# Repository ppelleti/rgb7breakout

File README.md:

Don't use this as-is; the footprint for D2 is wrong.

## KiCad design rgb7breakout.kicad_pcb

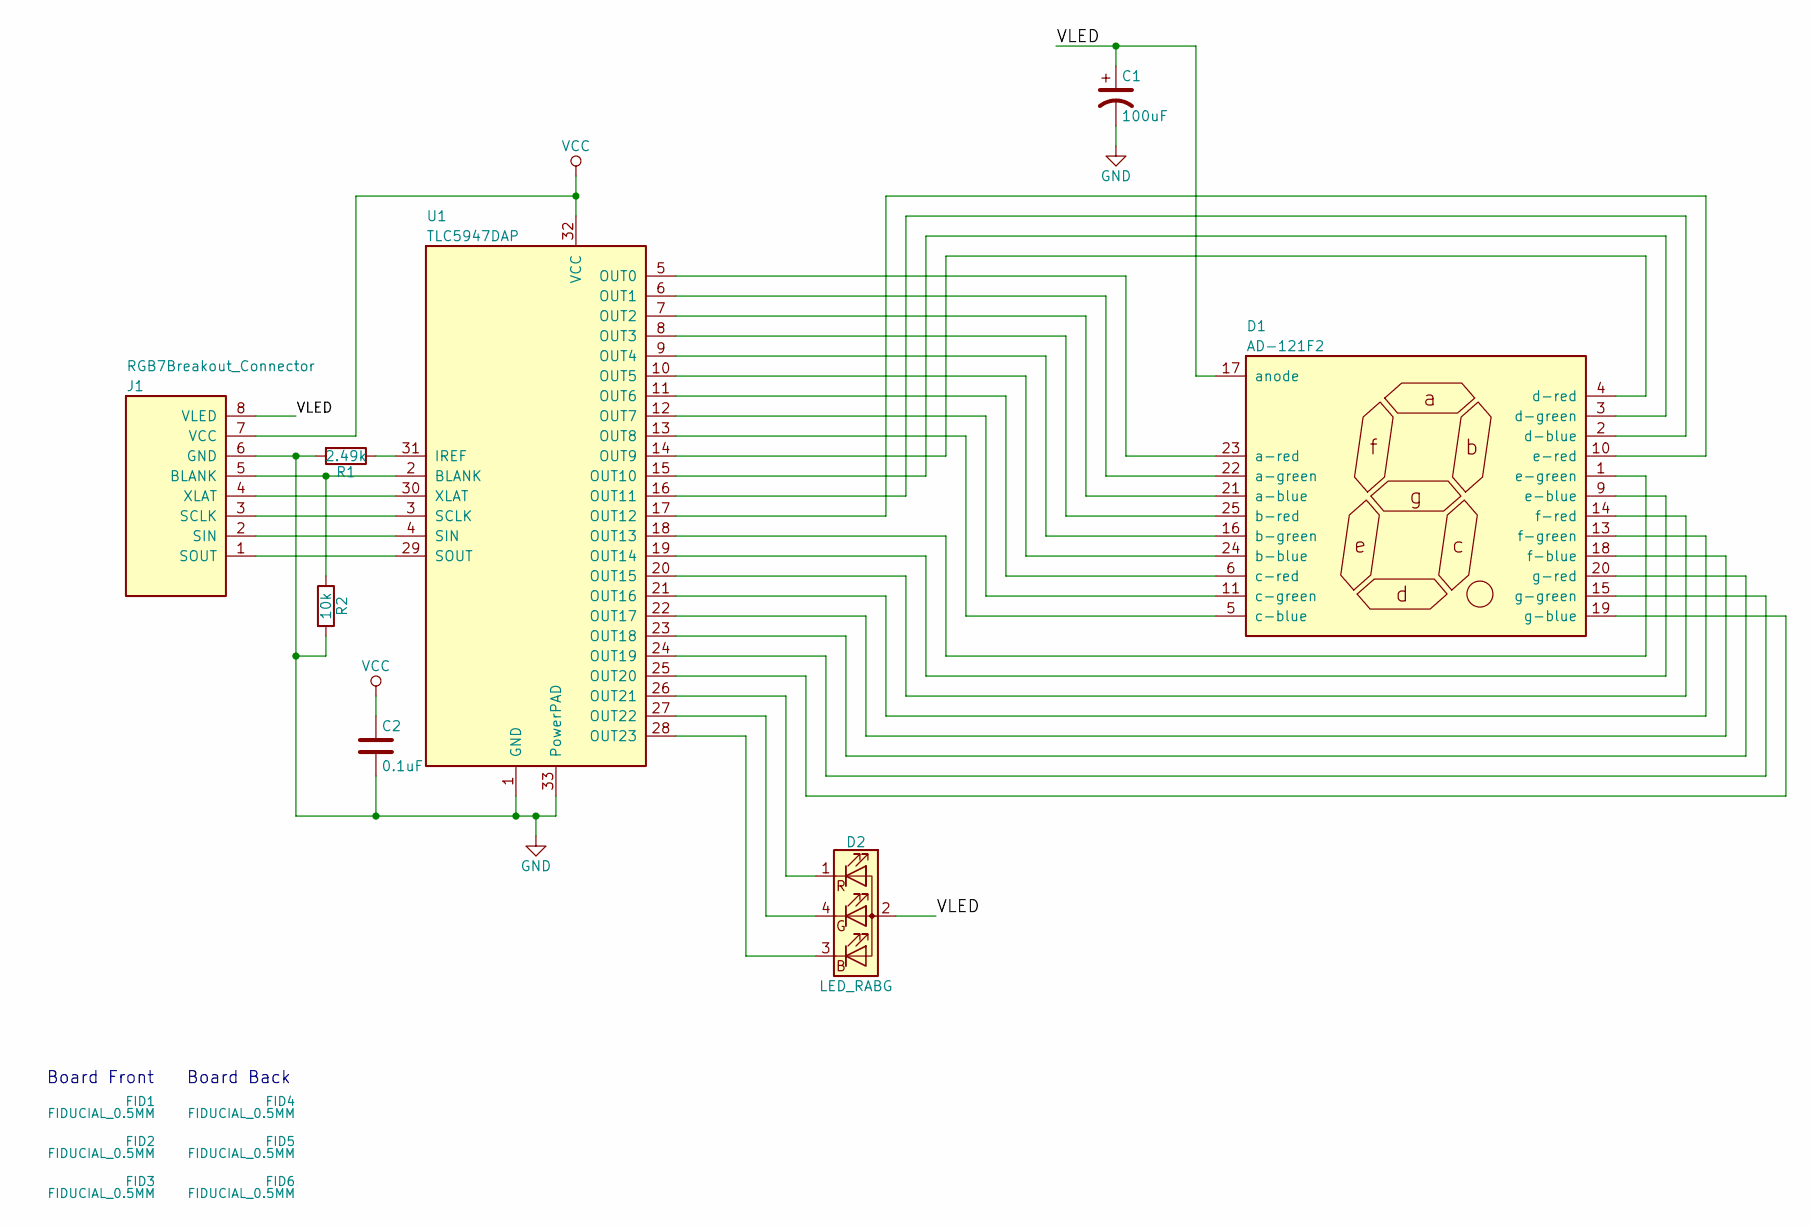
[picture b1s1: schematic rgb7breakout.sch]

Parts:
C1: 100uF; CP_Elec_6.3x7.7; mpn 107SML016M
C2: 0.1uF; C_0603; mpn MF-CAP-0603-0.1uF
D1: AD-121F2; mpn AD-121F2
D2: LED_RABG; LED_Cree-PLCC4; mpn CLV1A-FKB-CHMKPEHBB7A363
FID1, FID2, FID3, FID4, FID5, FID6: FIDUCIAL_0.5MM; MF_Aesthetics-FIDUCIAL_0.5MM
J1: RGB7Breakout_Connector; Pin_Header_Angled_1x08_Pitch2.54mm; mpn PRPC008SBAN-M71RC
R1: 2.49k; R_0603; mpn RC0603FR-072K49L
R2: 10k; R_0603; mpn MF-RES-0603-10K
U1: TLC5947DAP; HTSSOP-32_6.1x11mm_Pitch0.65mm_ThermalPad; mpn TLC5947DAP

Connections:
/VLED: C1.1, D1.17 (anode), D2.2 (A), J1.8 (VLED)
GND: C1.2, C2.2, J1.6 (GND), R1.2, R2.2, U1.1 (GND), U1.33 (PowerPAD)
unnamed: D1.1 (e-green), U1.18 (OUT13)
unnamed: D1.2 (d-blue), U1.16 (OUT11)
unnamed: D1.3 (d-green), U1.15 (OUT10)
unnamed: D1.4 (d-red), U1.14 (OUT9)
unnamed: D1.5 (c-blue), U1.13 (OUT8)
unnamed: D1.6 (c-red), U1.11 (OUT6)
unnamed: D1.9 (e-blue), U1.19 (OUT14)
unnamed: D1.10 (e-red), U1.17 (OUT12)
unnamed: D1.11 (c-green), U1.12 (OUT7)
unnamed: D1.13 (f-green), U1.21 (OUT16)
unnamed: D1.14 (f-red), U1.20 (OUT15)
unnamed: D1.15 (g-green), U1.24 (OUT19)
unnamed: D1.16 (b-green), U1.9 (OUT4)
unnamed: D1.18 (f-blue), U1.22 (OUT17)
unnamed: D1.19 (g-blue), U1.25 (OUT20)
unnamed: D1.20 (g-red), U1.23 (OUT18)
unnamed: D1.21 (a-blue), U1.7 (OUT2)
unnamed: D1.22 (a-green), U1.6 (OUT1)
unnamed: D1.23 (a-red), U1.5 (OUT0)
unnamed: D1.24 (b-blue), U1.10 (OUT5)
unnamed: D1.25 (b-red), U1.8 (OUT3)
unnamed: D2.1 (RK), U1.26 (OUT21)
unnamed: D2.3 (BK), U1.28 (OUT23)
unnamed: D2.4 (GK), U1.27 (OUT22)
unnamed: J1.1 (SOUT), U1.29 (SOUT)
unnamed: J1.2 (SIN), U1.4 (SIN)
unnamed: J1.3 (SCLK), U1.3 (SCLK)
unnamed: J1.4 (XLAT), U1.30 (XLAT)
unnamed: J1.5 (BLANK), R2.1, U1.2 (BLANK)
unnamed: R1.1, U1.31 (IREF)
VCC: C2.1, J1.7 (VCC), U1.32 (VCC)

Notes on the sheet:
Board Front
Board Back

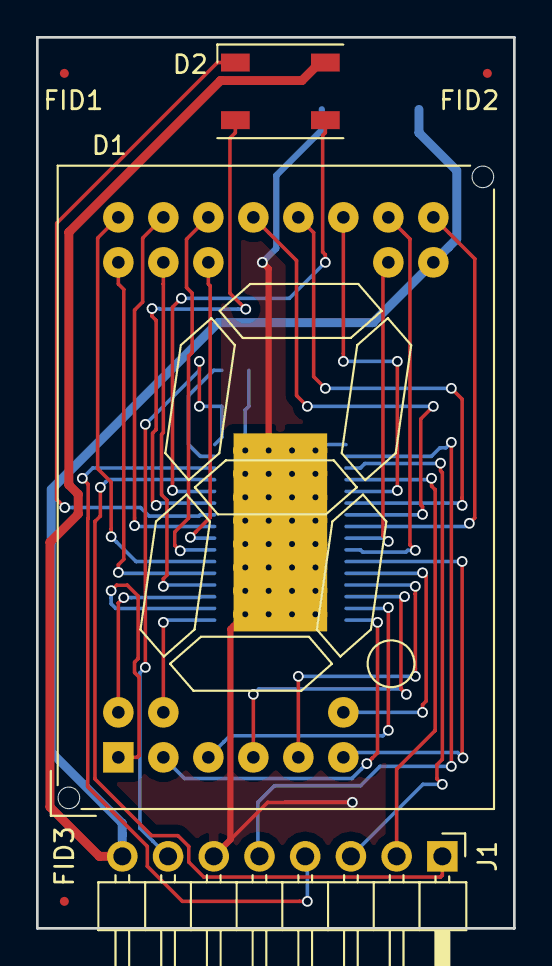
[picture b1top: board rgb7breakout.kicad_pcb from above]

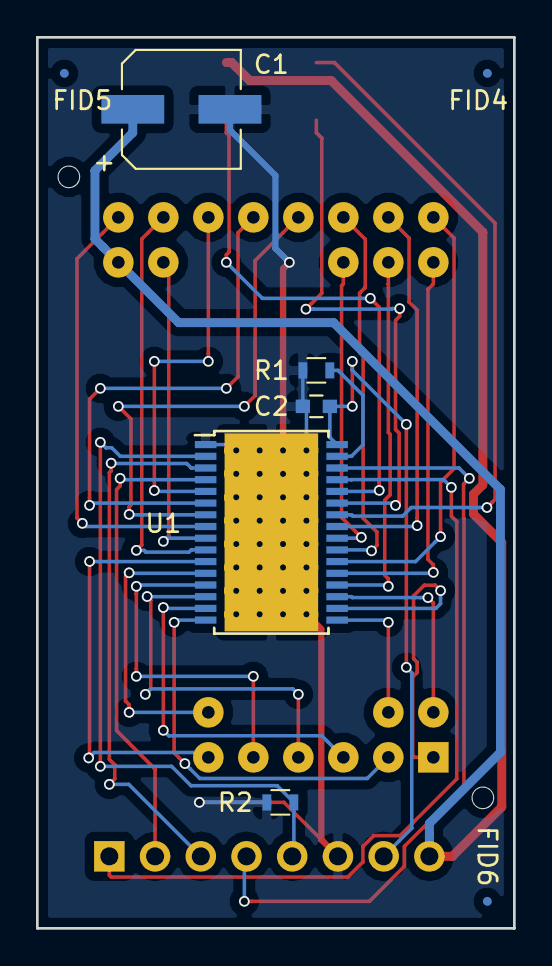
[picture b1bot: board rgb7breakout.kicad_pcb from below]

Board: 2 copper layers, 26.5 x 49.5 mm, 14 parts (8 on the bottom side), 33 nets.

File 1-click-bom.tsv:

References	Qty	description	mpn
C1	1	CAP ALUM 100UF 20% 16V SMD	107SML016M
C2	1	Capacitor MLCC 0603 0.1uF 10% 25V	MF-CAP-0603-0.1uF
D1	1	Single Digit 7-segment RGB LED Display, 1-inch digit height, common anode	AD-121F2
D2	1	LED RGB DIFFUSED 4LCC SMD	CLV1A-FKB-CHMKPEHBB7A363
FID1, FID2, FID3, FID4, FID5, FID6	6		
J1	1	"CONN HEADER .100"" SNGL R/A 8POS"	PRPC008SBAN-M71RC
R1	1	RES SMD 2.49K OHM 1% 1/10W 0603	RC0603FR-072K49L
R2	1	Resistor Thick Film 0603 10K Ohm 5% 100mW 75V	MF-RES-0603-10K
U1	1	24-Channel, 12-Bit PWM LED Driver, HTSSOP	TLC5947DAP

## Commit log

2017-09-12 add library
2017-09-12 add myLibrary to list of libraries
2017-09-12 add two main components to schematic
2017-09-12 add RGB LED
2017-09-12 add symbol for board connector
2017-09-12 add resistor and some wires
2017-09-12 draw some more wires
2017-09-12 finish wires to LEDs
2017-09-12 added some decoupling capacitors
2017-09-12 use house parts for capacitors
2017-09-12 pulldown resistor for BLANK
2017-09-12 use QFN package instead of HTSSOP
2017-09-12 annotated components
2017-09-12 footprint for 7-segment RGB LED
2017-09-12 assigned footprints
2017-09-12 initial placement
2017-09-12 move some labels
2017-09-12 set up DRC
2017-09-13 Revert "use QFN package instead of HTSSOP"
    This reverts commit 53edefbe48f0738e924cbb3b128b6e9d93a24fb3.
    Conflicts:
    rgb7breakout.sch
2017-09-13 fix error from revert
2017-09-13 add HTSSOP-32 footprint
2017-09-13 associate HTSSOP-32 footprint with TLC5947
2017-09-13 add libraries for fiducials
2017-09-13 add fiducials to schematic
2017-09-13 initial placement of HTSSOP and fiducials
2017-09-13 add fiducials on back side of board, too
2017-09-13 routed most of the LED tracks
2017-09-13 routed more LED tracks
2017-09-13 finished routing all tracks
2017-09-13 added ground planes on both sides
2017-09-13 forgot to route VCC
2017-09-13 connected up GND manually
2017-09-13 passes DRC
2017-09-13 increase width of GND tracks
2017-09-13 switch back to Illinois Capacitor
2017-09-13 fill out manufacturer part numbers
2017-09-13 rename ManufacturerPartNumber to mpn
2017-09-13 generate BOM
2017-09-13 gerber settings for MacroFab
2017-09-13 generated gerbers
2017-09-13 add .DS_Store to .gitignore
2017-10-19 KiCad inexplicably changed the .pro file.
2017-10-19 Warn about D2 footprint being incorrect.
